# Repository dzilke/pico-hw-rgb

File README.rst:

Extension board for Raspberry Pi Pico
=====================================

This pcb is designed as an extension for the Raspberry Pi Pico microcontroller. It features two red-green-blue leds, a button and a `Pmod interface <https://digilent.com/reference/pmod/start>`_.

.. figure:: figures/PicoBoard.png

Special thanks to Karl Dören for his work!

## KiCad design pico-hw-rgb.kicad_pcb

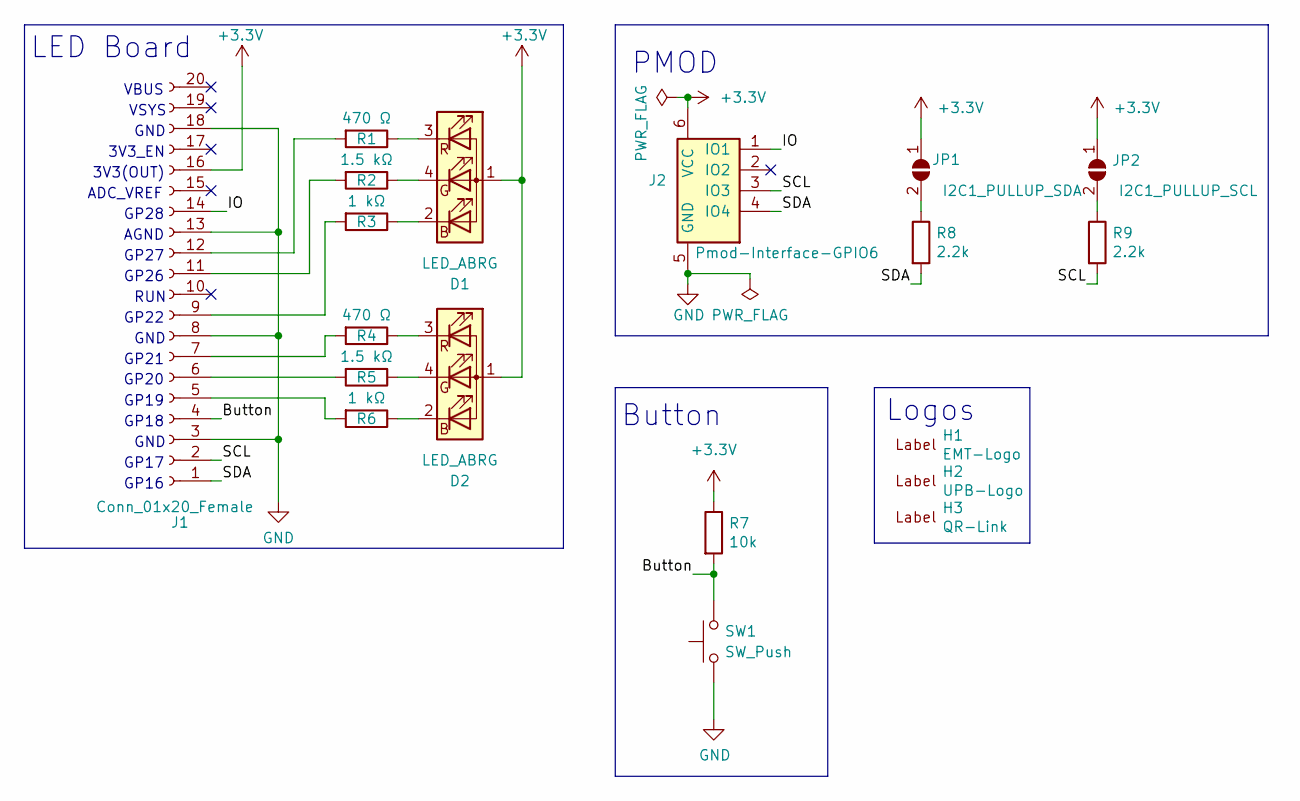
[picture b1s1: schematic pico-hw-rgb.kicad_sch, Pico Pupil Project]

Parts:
D1, D2: LED_ABRG; LED_RGB_Wuerth-PLCC4_3.2x2.8mm_150141M173100
H1: EMT-Logo; EMT-Logo_11.7x5.9mm_Silkscreen
H2: UPB-Logo; UPB-Logo_De_15.9X5.6mm
H3: QR-Link; qr-studiere-et_15x16
J1: Conn_01x20_Female; PinSocket_1x20_P2.54mm_Vertical
J2: Pmod-Interface-GPIO6; Pmod_Interface_Female6
JP1: I2C1_PULLUP_SDA; SolderJumper-2_P1.3mm_Open_TrianglePad1.0x1.5mm
JP2: I2C1_PULLUP_SCL; SolderJumper-2_P1.3mm_Open_TrianglePad1.0x1.5mm
R1, R4: 470 Ω; R_0603_1608Metric
R2, R5: 1.5 kΩ; R_0603_1608Metric
R3, R6: 1 kΩ; R_0603_1608Metric
R7: 10k; R_0603_1608Metric
R8, R9: 2.2k; R_0603_1608Metric
SW1: SW_Push; SW_SPST_Schurter_1301.93XX

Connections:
+3.3V: D1.1 (A), D2.1 (A), J1.16, J2.6 (VCC), JP1.1 (A), JP2.1 (A), R7.1
/Button: J1.4, R7.2, SW1.2
/IO: J1.14, J2.1 (IO1)
/SCL: J1.2, J2.3 (IO3), R9.2
/SDA: J1.1, J2.4 (IO4), R8.2
GND: J1.3, J1.8, J1.13, J1.18, J2.5 (GND), SW1.1
unnamed: D1.2 (BK), R3.1
unnamed: D1.3 (RK), R1.1
unnamed: D1.4 (GK), R2.1
unnamed: D2.2 (BK), R6.1
unnamed: D2.3 (RK), R4.1
unnamed: D2.4 (GK), R5.1
unnamed: J1.5, R6.2
unnamed: J1.6, R5.2
unnamed: J1.7, R4.2
unnamed: J1.9, R3.2
unnamed: J1.11, R2.2
unnamed: J1.12, R1.2
unnamed: JP1.2 (B), R8.1
unnamed: JP2.2 (B), R9.1

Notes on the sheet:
3V3(OUT)
AGND
ADC_VREF
GP20
GP17
GP27
GP28
Logos
GP18
GP19
PMOD
VSYS
GP21
RUN
GP26
GND
VBUS
Button
3V3_EN
GP16
GP22
LED Board

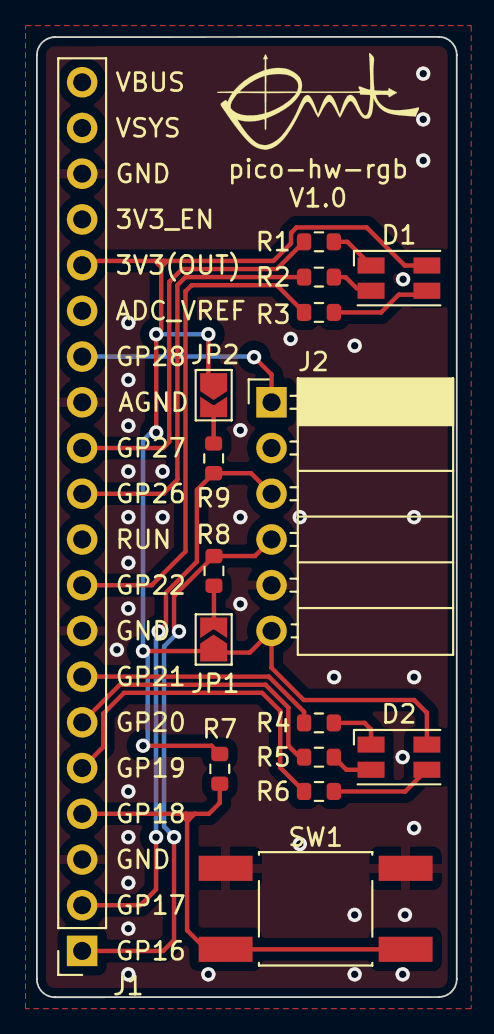
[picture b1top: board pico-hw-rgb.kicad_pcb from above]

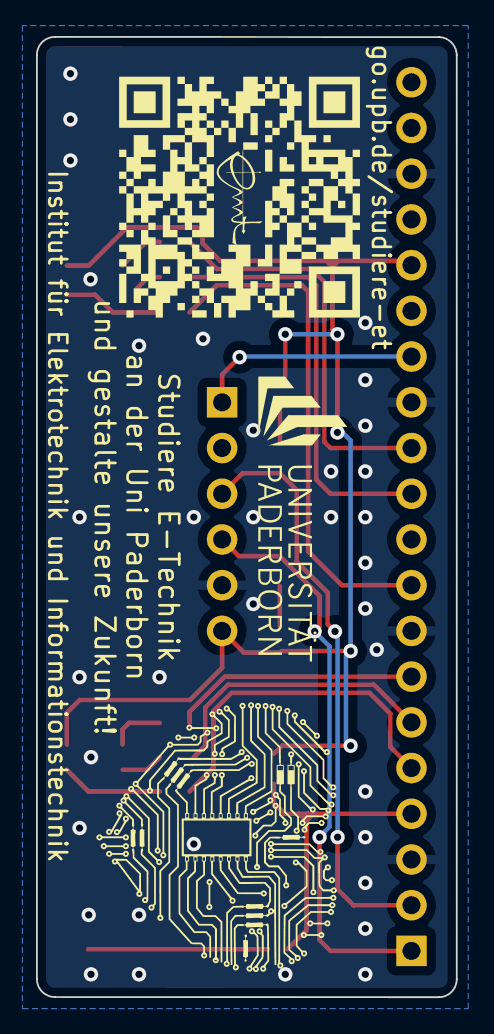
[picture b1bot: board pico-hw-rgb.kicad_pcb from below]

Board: 2 copper layers, 23.3 x 53.3 mm, 19 parts (2 on the bottom side), 20 nets.

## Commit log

2023-11-09 Add readme
2023-11-10 Add project
2023-11-21 Add additional footprint 'infinity'
2025-05-22 Add interactive BOM link
